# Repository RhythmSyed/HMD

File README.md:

# HMD
ECE 477 Team 6

HMD is a wearable Health Monitoring Device that provides the user with real-time health information through a continuous stream to the cloud and to a companion app for client-side use. The system includes a wide variety of sensors that allow the device to monitor the activity of the user through step tracking and monitoring sleep quality. To ensure uninterrupted wear, the battery level of the device is recorded to insure the device is always powered. The system also includes an alert system for sleep reminders, low battery levels, and alerts to family members in case of health concerns. The system will also incorporate a display attached to the wearable informing the user his total steps and the battery percentage of the device.

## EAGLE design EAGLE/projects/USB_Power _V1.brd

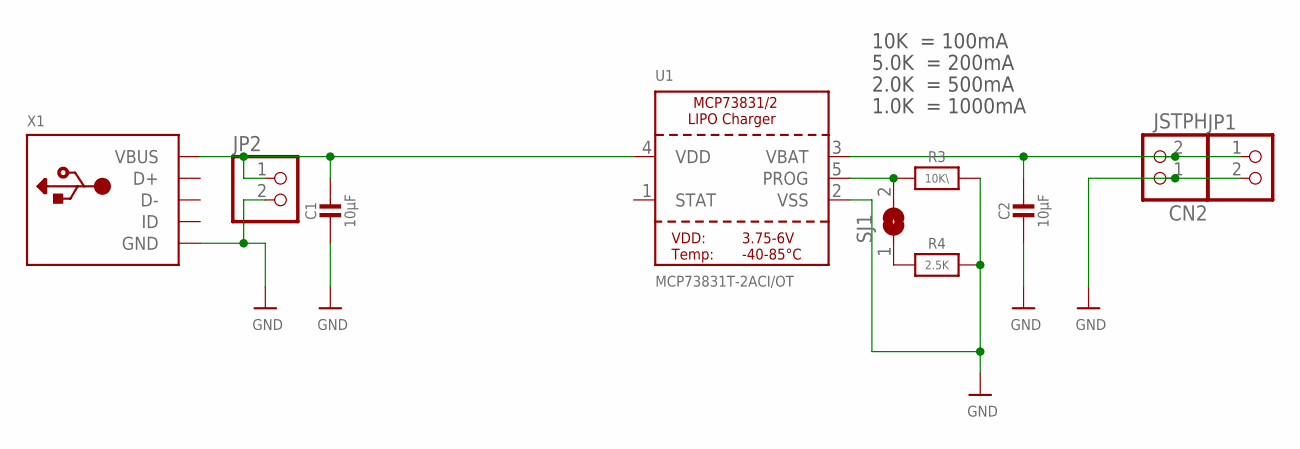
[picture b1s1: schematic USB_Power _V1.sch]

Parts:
C1, C2: 10µF; 0805-NO
CN2: JSTPH; JSTPH2
JP1, JP2: HEADER-1X2ROUND; 1X02_ROUND
R3: 10K\; 0805-NO
R4: 2.5K; 0805-NO
SJ1: SOLDERJUMPER; SOLDERJUMPER_ARROW_NOPASTE
U1: MCP73831T-2ACI/OT; SOT23-5
X1: USB_MEDIUM; USB-MINI_MEDIUM

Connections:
GND: C1.2, C2.2, CN2.1, JP1.2, JP2.2, R3.2, R4.2, U1.2 (VSS), X1.GND, X1.GND1 (GND), X1.GND2 (GND), X1.GND3 (GND), X1.GND4 (GND)
unnamed: R4.1, SJ1.1
unnamed: R3.1, SJ1.2, U1.5 (PROG)
VBAT: C2.1, CN2.2, JP1.1, U1.3 (VBAT)
VDD: C1.1, JP2.1, U1.4 (VDD), X1.VBUS

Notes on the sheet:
10K = 100mA
5.0K = 200mA
2.0K = 500mA
1.0K = 1000mA

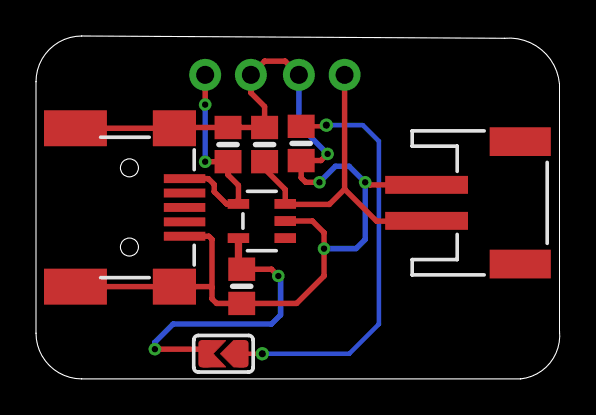
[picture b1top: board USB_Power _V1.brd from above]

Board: 2 copper layers, 29.1 x 19.1 mm, 10 parts (0 on the bottom side), 5 nets.

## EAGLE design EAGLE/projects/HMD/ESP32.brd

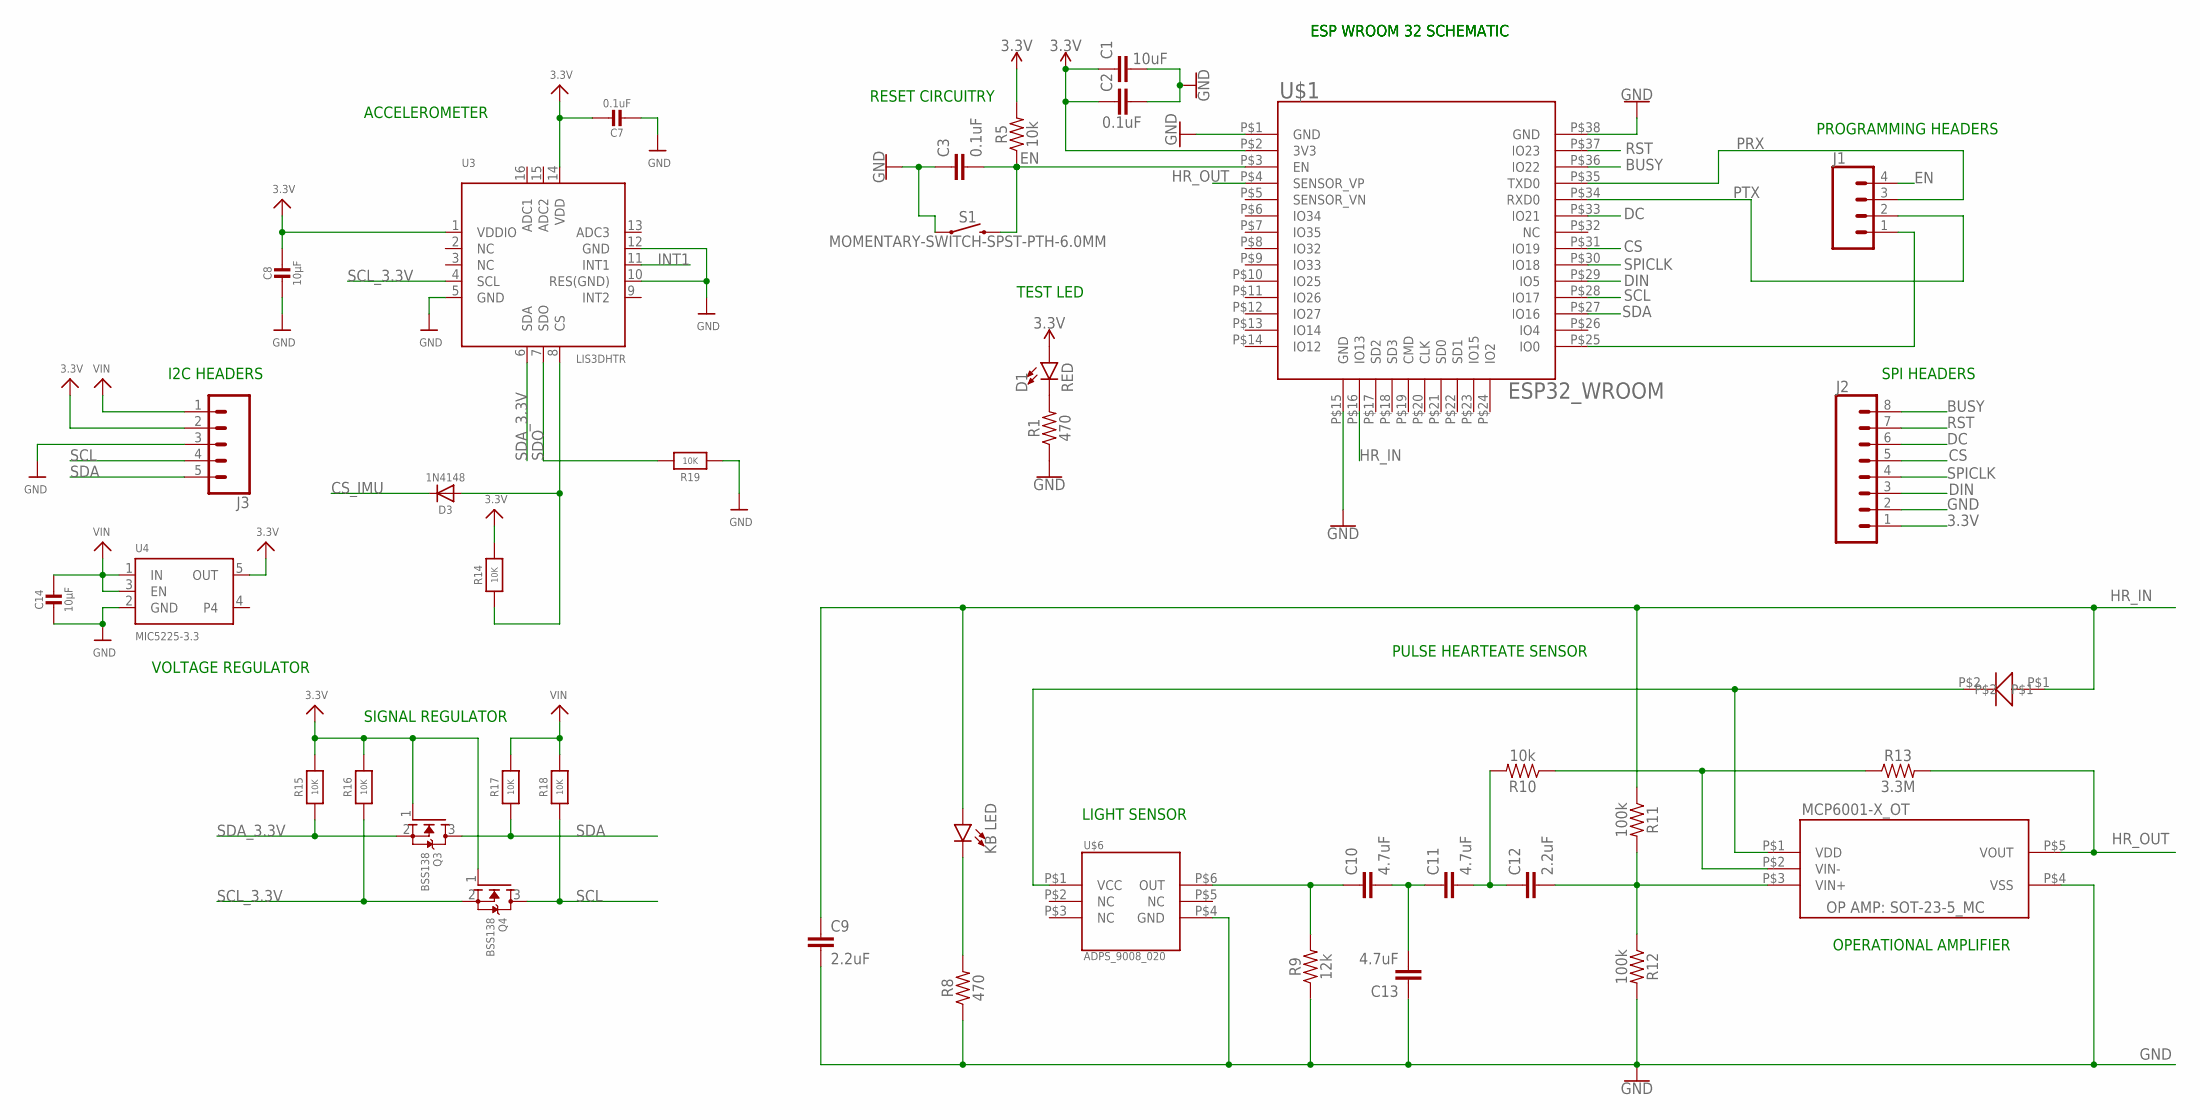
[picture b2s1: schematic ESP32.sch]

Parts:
C1: 10uF; 0603
C2, C3: 0.1uF; 0603
C7: 0.1uF; _0603MP
C8, C14: 10µF; _0603
C9, C12: 2.2uF; 0603
C10, C11, C13: 4.7uF; 0603
D1: RED; LED-0603
D3: 1N4148; SOD-323
J1: CONN_04; 1X04
J2: CONN_08"; 1X08
J3: CONN_05; 1X05
Q3, Q4: BSS138; SOT23-WIDE
R1, R8: 470; 0603
R5, R10: 10k; 0603
R9: 12k; 0603
R11, R12: 100k; 0603
R13: 3.3M; 0603
R14, R15, R16, R17, R18, R19: 10K; _0603
S1: MOMENTARY-SWITCH-SPST-PTH-6.0MM; TACTILE_SWITCH_PTH_6.0MM
U3: LIS3DHTR; LGA16_3X3MM
U4: MIC5225-3.3; SOT23-5
U$1: ESP32_WROOM; ESP32_FP
U$5: MCP6001-X_SOT-23-5; SOT-23-5
U$6: ADPS_9008_020; ADPS_FP
U$7: KB_REVMNT_LED; REVMNT_LED_FP
U$8: DI0603; DIODE0603

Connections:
3.3V: C1.1, C2.1, C7.1, C8.1, D1.A, J2.1, J3.2, Q3.1 (G), Q4.1 (G), R5.2, R14.2, R15.2, R16.2, U3.1 (VDDIO), U3.14 (VDD), U4.5 (OUT), U$1.P$2 (3V3)
BUSY: J2.8, U$1.P$36 (IO22)
CS: J2.5, U$1.P$31 (IO19)
CS_IMU: D3.C
DC: J2.6, U$1.P$33 (IO21)
DIN: J2.3, U$1.P$29 (IO5)
EN: C3.2, J1.4, R5.1, S1.3 (2), U$1.P$3 (EN)
GND: C1.2, C2.2, C3.1, C7.2, C8.2, C9.2, C13.1, C14.2, J2.2, J3.3, R1.1, R8.1, R9.1, R12.2, R19.1, S1.1, U3.5 (GND), U3.10 (RES(GND)), U3.12 (GND), U4.2 (GND), U$1.P$1 (GND), U$1.P$15 (GND), U$1.P$38 (GND), U$5.P$4 (VSS), U$6.P$4 (GND)
HR_IN: C9.1, R11.1, U$1.P$16 (IO13), U$7.P$1 (A), U$8.P$1
HR_OUT: R13.2, U$1.P$4 (SENSOR_VP), U$5.P$5 (VOUT)
INT1: U3.11 (INT1)
unnamed: D3.A, R14.1, U3.8 (CS)
unnamed: D1.C, R1.2
unnamed: J1.1, U$1.P$25 (IO0)
unnamed: C10.1, R9.2, U$6.P$6 (OUT)
unnamed: C10.2, C11.1, C13.2
unnamed: C11.2, C12.1, R10.2
unnamed: C12.2, R11.2, R12.1, U$5.P$3 (VIN+)
unnamed: R10.1, R13.1, U$5.P$2 (VIN-)
unnamed: U$5.P$1 (VDD), U$6.P$1 (VCC), U$8.P$2
unnamed: R8.2, U$7.P$2 (C)
PRX: J1.3, U$1.P$35 (TXD0)
PTX: J1.2, U$1.P$34 (RXD0)
RST: J2.7, U$1.P$37 (IO23)
SCL: J3.4, Q4.3 (D), R18.1, U$1.P$28 (IO17)
SCL_3.3V: Q4.2 (S), R16.1, U3.4 (SCL)
SDA: J3.5, Q3.3 (D), R17.1, U$1.P$27 (IO16)
SDA_3.3V: Q3.2 (S), R15.1, U3.6 (SDA)
SDO: R19.2, U3.7 (SDO)
SPICLK: J2.4, U$1.P$30 (IO18)
VIN: C14.1, J3.1, R17.2, R18.2, U4.1 (IN), U4.3 (EN)

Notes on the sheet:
ESP WROOM 32 SCHEMATIC
SPI HEADERS
PULSE HEARTEATE SENSOR
OPERATIONAL AMPLIFIER
LIGHT SENSOR
RESET CIRCUITRY
I2C HEADERS
PROGRAMMING HEADERS
VOLTAGE REGULATOR
ACCELEROMETER
SIGNAL REGULATOR
TEST LED

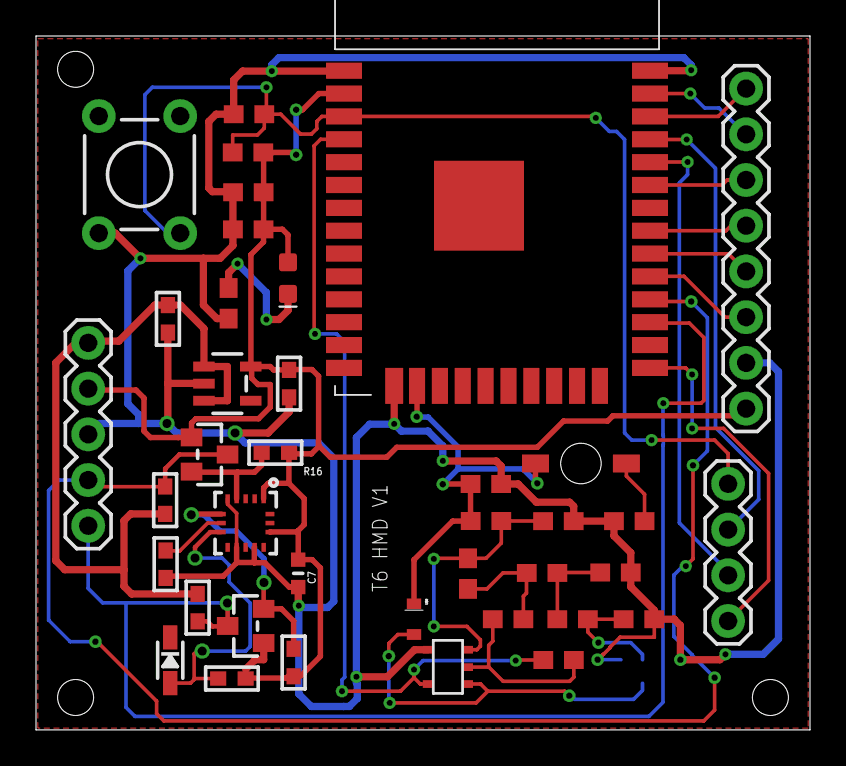
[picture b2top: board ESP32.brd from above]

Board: 2 copper layers, 43.0 x 38.5 mm, 40 parts (1 on the bottom side), 29 nets.

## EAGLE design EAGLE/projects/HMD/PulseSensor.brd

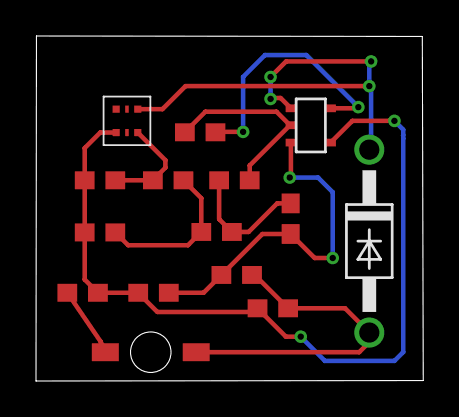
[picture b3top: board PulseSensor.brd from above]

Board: 2 copper layers, 21.5 x 19.2 mm, 15 parts (0 on the bottom side), 10 nets.

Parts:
C1, C2, C3: 4.7uF; 0603
C4, C5: 2.2uF; 0603
D1: 1N4004; DO41-10
R1: 470; 0603
R2: 12k; 0603
R3, R4: 100k; 0603
R5: 10k; 0603
R6: 3.3M; 0603
U$1: ADPS_9008_020; ADPS_FP
U$2: KB_REVMNT_LED; REVMNT_LED_FP
U$3: MCP6001-X_SOT-23-5; SOT-23-5

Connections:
3.3V: C5.1, D1.A, R4.1, U$2.P$1
GND: C1.1, C5.2, R1.1, R2.1, R3.2, U$1.P$4, U$3.P$4
HR_OUT: R6.2, U$3.P$5
unnamed: C2.1, R2.2, U$1.P$6
unnamed: C1.2, C2.2, C3.1
unnamed: C3.2, C4.1, R5.2
unnamed: C4.2, R3.1, R4.2, U$3.P$3
unnamed: R1.2, U$2.P$2
unnamed: R5.1, R6.1, U$3.P$2
unnamed: D1.C, U$1.P$1, U$3.P$1

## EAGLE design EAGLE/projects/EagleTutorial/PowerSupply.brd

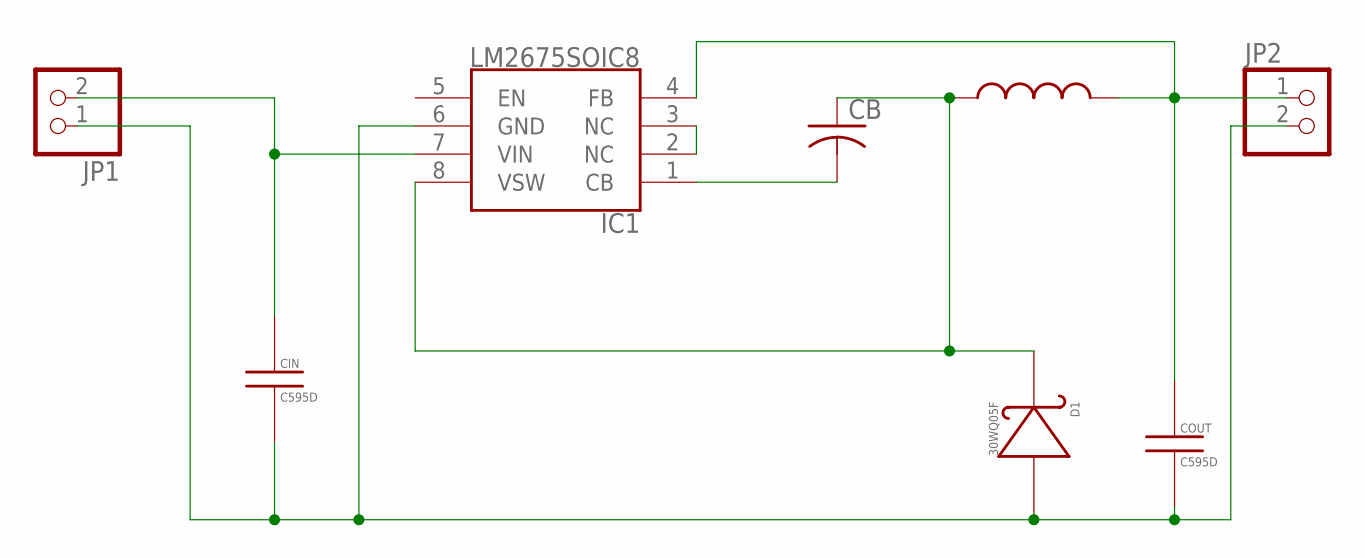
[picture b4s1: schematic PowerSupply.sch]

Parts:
CB: 0.01uF; C1206
CIN: C595D; C_595D
COUT: C595D; C_595D
D1: 30WQ05F; D_SMA
IC1: LM2675SOIC8; SO8
JP1, JP2: PINHD-1X2; 1X02
L: SDR1005L_SMD_V; L_SMD

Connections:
unnamed: CIN.P$2, IC1.7 (VIN), JP1.2
unnamed: CIN.P$1, COUT.P$1, D1.P$1, IC1.6 (GND), JP1.1, JP2.2
unnamed: COUT.P$2, IC1.4 (FB), JP2.1, L.P$1
unnamed: CB.1, D1.P$2, IC1.8 (VSW), L.P$2
unnamed: CB.2, IC1.1 (CB)
unnamed: IC1.2 (NC), IC1.3 (NC)

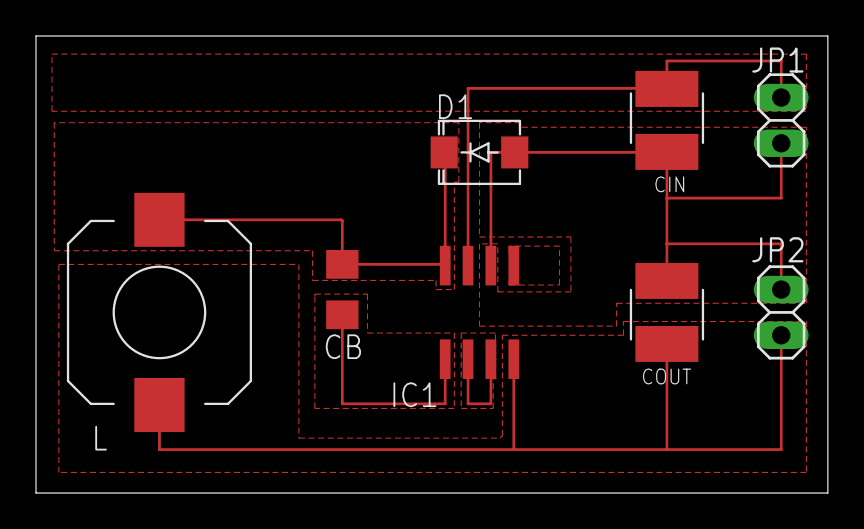
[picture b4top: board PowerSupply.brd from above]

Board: 2 copper layers, 44.0 x 25.4 mm, 8 parts (0 on the bottom side), 6 nets.

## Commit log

2019-01-23 initial proj setup, blink LED
2019-01-25 added awsdemo for esp32
2019-01-26 file structure for rtos
2019-01-27 reconfigure dir
2019-01-27 fresh project
2019-02-01 added more tests
2019-02-01 added companion app template
2019-02-02 Added basic ADC to main.c
2019-02-02 Added thresholds that are able to detect a heart beat in the thumb
2019-02-08 restructed for ble
2019-02-08 Added heart beat file and code
2019-02-13 got rid of amazonFreertos
2019-02-13 ble, HR, and blink tasks working
2019-02-13 ble advertisement
2019-02-13 file structure
2019-02-13 stuff
2019-02-13 working MPU, changed files to cpp to support mpu library
2019-02-14 Heart Rate & ESP32 footprints
2019-02-15 working mpu sensor in C
2019-02-16 Added display interface, add folder under "components" into "esp/esp-idf/components"
2019-02-16 Layout for PulseSensor & Schematic for ESP32
2019-02-18 Fixed display to compile
2019-02-19 Changed the display API to work with the 1.45 inch display. Added a HMD demo for display
2019-02-20 Made SPI initialization in esp-epaper-29-ws.c Changed library, need to update components/epaper-29-ws/epaper-29-ws.c and components/epaper-29-ws/epaper-29-ws.h
2019-02-20 Added GPIO initialization outside of library
2019-02-21 BLE server working
2019-02-22 Changed name of epaper_display.c Added back components/ folder.
2019-02-22 organized code, added modes
2019-02-22 working mode toggle from app
2019-02-23 cleanup, modularized heartrate
2019-02-23 Add files via upload
    IMU Design Block
2019-02-24 added temp files
2019-02-24 PCB layed out
2019-02-24 Merged
2019-02-28 ble: mcu to app working for heartrate
2019-02-28 app edits
2019-03-01 working mpu on app. need to figure out display management for tasks. Recalling MPU display causes crash
2019-03-01 working ble for app, samples sensor data every 30 secs
2019-03-05 Changes components/epaper-29-ws/epaper-29-ws.c to use partial update LUT
2019-03-14 Changed components/epaper-29-ws/epaper-29-ws.c , Created layout for ActivityMode
2019-03-18 Created sleep mode display
2019-03-20 Version 1 micro
2019-03-20 Revert "stuff"
    This reverts commit c9592abd68b907ec920e2058757725e4ef075ec8.
2019-03-20 Revert "Version 1 micro"
    This reverts commit 22c8d65d876e5e97d8f3c243cdc0f8aa191d734f.
2019-03-20 Final Version 1 PCB
2019-03-25 adding app and backend updates
2019-03-29 working LIS3dh code, cloud updates
2019-03-29 updated IMU code, currently working
2019-04-01 dynamoDB configured, collecting data now
2019-04-01 added UI template, working on integrating with current functionality
2019-04-03 Added display_data struct for intertask communication
2019-04-03 dram data errors
2019-04-05 all tasks working together w/ shared data structure
2019-04-08 working step tracking
2019-04-10 artificial heart rate
2019-04-17 sleepquality lambda fnx done, base usage case done
2019-04-22 Made HR smoother. Need to uncomment tasks in main.c

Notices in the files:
parts and their libraries:
SparkFun-Capacitors: Licensing: Creative Commons ShareAlike 4.0 International - https://creativecommons.org/licenses/by-sa/4.0
microbuilder: This work is placed in the public domain, and may be freely used for commercial and non-commercial work with the following conditions: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
